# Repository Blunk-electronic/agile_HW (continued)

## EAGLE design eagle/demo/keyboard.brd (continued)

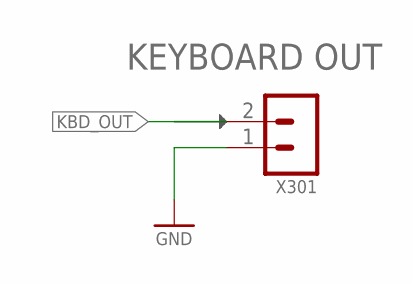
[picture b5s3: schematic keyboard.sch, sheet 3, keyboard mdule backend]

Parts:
X301: MALE_2X1-T-VERTICAL; T_MALE_2X1_VERTICAL_PITCH_2MM54

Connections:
GND: X301.1; also elsewhere on the board
KBD_OUT: X301.2; also elsewhere on the board

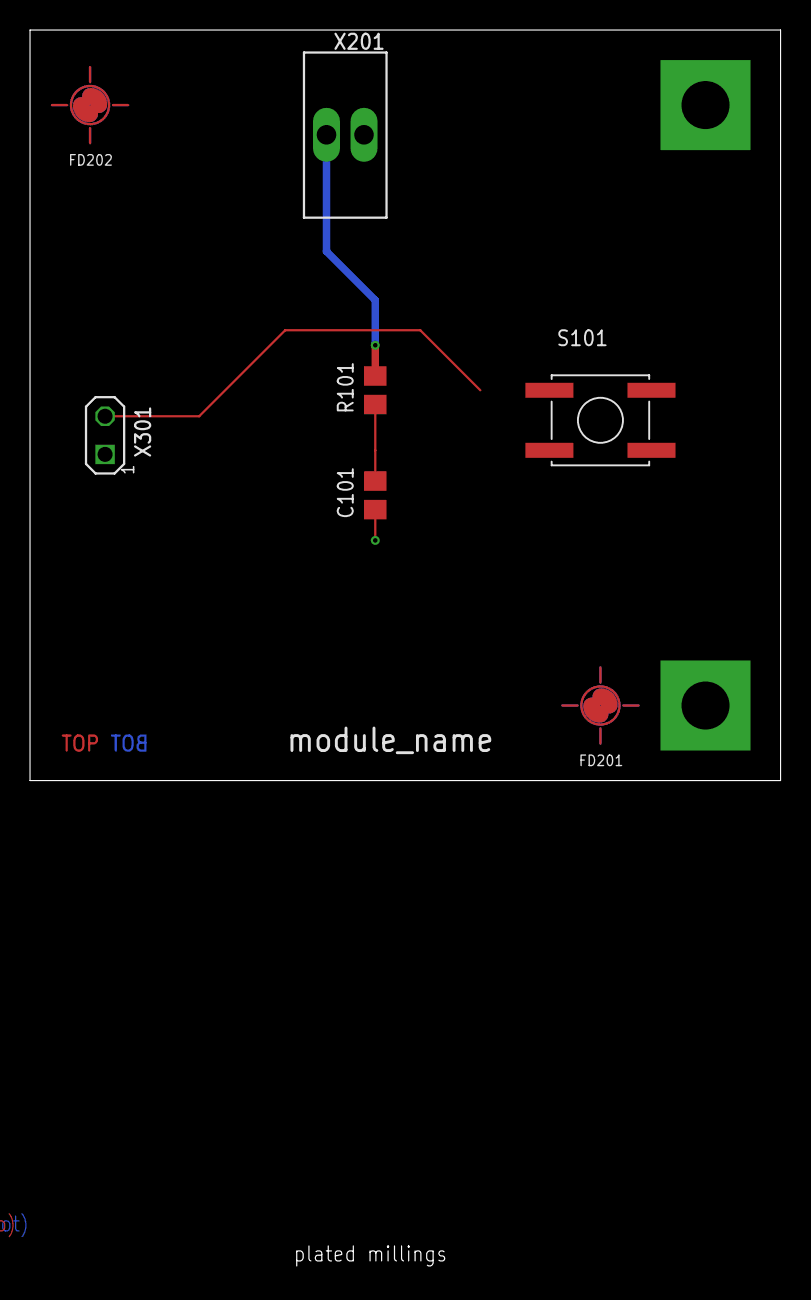
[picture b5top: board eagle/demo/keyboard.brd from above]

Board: 4 copper layers, 50.0 x 82.6 mm, 10 parts (0 on the bottom side), 3 nets.

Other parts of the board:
U$5: A4_LANDSCAPE

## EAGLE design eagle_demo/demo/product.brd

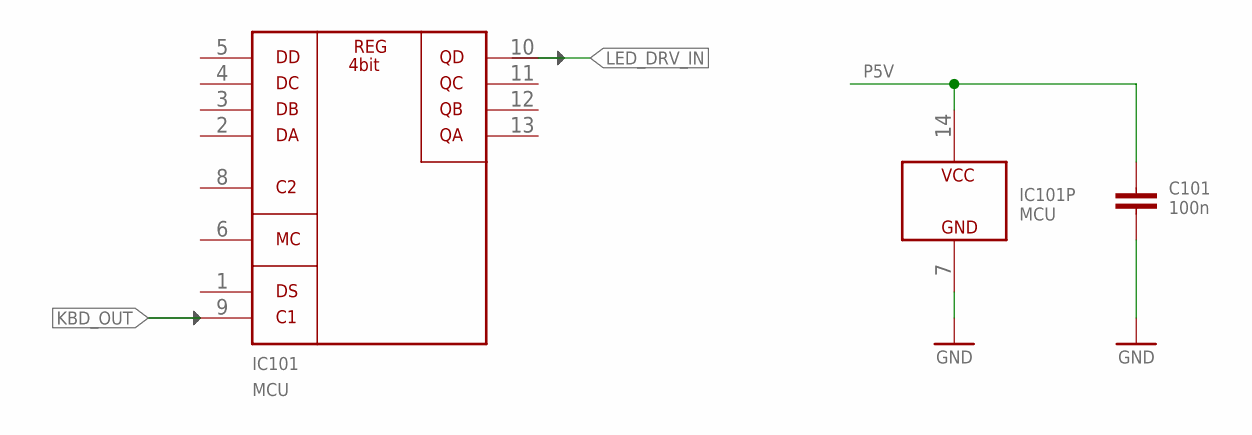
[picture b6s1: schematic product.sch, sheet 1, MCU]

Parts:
C101: 100n; S_0603
IC101: MCU; S_SO14

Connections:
GND: C101.2, IC101.7 (GND); also elsewhere on the board
KBD_OUT: IC101.9 (C1); also elsewhere on the board
LED_DRV_IN: IC101.10 (QD); also elsewhere on the board
P5V: C101.1, IC101.14 (VCC); also elsewhere on the board

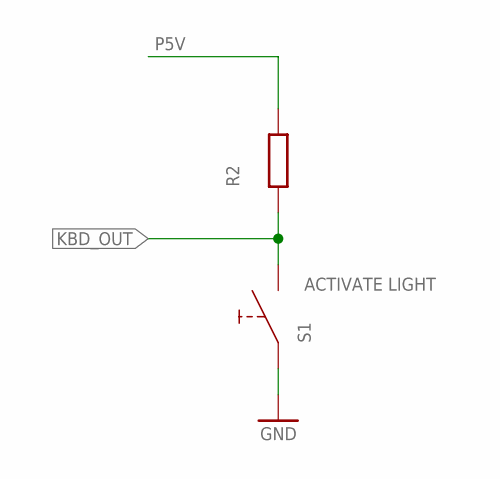
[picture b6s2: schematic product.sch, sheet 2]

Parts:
R2: R_S_0603; S_0603
S1: PUSH_BUTTON_S_6X6MM; S_PUSH_BUTTON_6X6

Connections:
GND: S1.A (A1), S1.A1; also elsewhere on the board
KBD_OUT: R2.1, S1.B (B1), S1.B1; also elsewhere on the board
P5V: R2.2; also elsewhere on the board

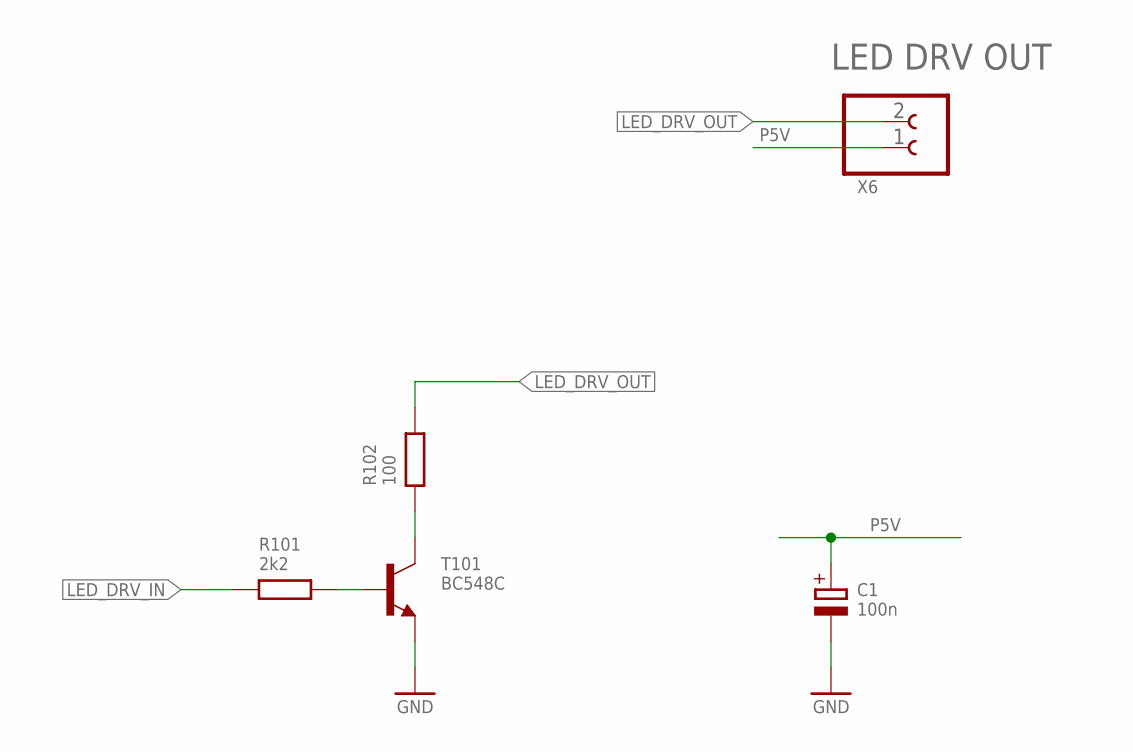
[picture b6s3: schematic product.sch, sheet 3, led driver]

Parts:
C1: 100n; S_3216-18
R101: 2k2; S_0603
R102: 100; S_0603
T101: BC548C; S_SOT23
X6: CLAMP_1X2-T-2.5MM; T_WIRE_CLAMP_1X2_PITCH_2MM5

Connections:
GND: C1.-, T101.2 (E); also elsewhere on the board
LED_DRV_B: R101.2, T101.1 (B)
LED_DRV_C: R102.1, T101.3 (C)
LED_DRV_IN: R101.1; also elsewhere on the board
LED_DRV_OUT: R102.2, X6.2
P5V: C1.+, X6.1; also elsewhere on the board

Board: 2 copper layers, 9 parts (0 on the bottom side), 7 nets, no tracks yet.

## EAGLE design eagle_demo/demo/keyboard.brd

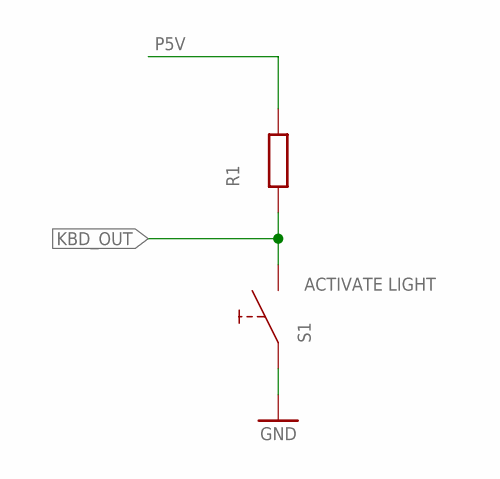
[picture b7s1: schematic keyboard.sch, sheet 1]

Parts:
R1: R_S_0805; S_0805
S1: PUSH_BUTTON_S_6X6MM; S_PUSH_BUTTON_6X6

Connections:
GND: S1.A (A1), S1.A1; also elsewhere on the board
KBD_OUT: R1.1, S1.B (B1), S1.B1; also elsewhere on the board
P5V: R1.2; also elsewhere on the board

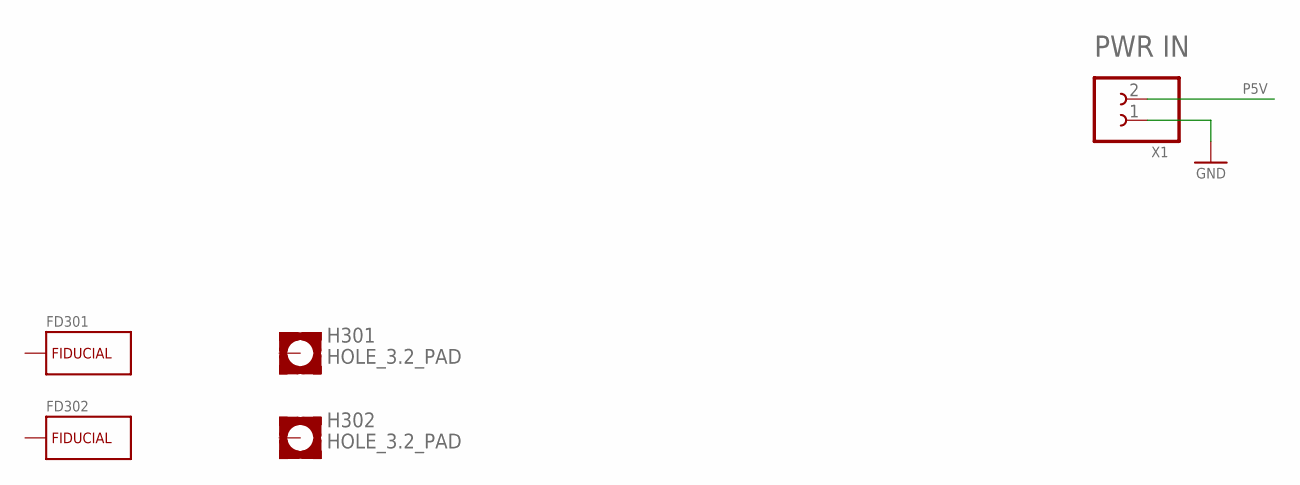
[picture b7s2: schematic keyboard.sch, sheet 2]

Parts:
FD301, FD302: FIDUCIAL_CROSSHAIR; CROSSHAIR
H301, H302: HOLE_3.2_PAD; 3.2_PAD
X1: CLAMP_1X2-T-2.5MM; T_WIRE_CLAMP_1X2_PITCH_2MM5

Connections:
GND: X1.1; also elsewhere on the board
P5V: X1.2; also elsewhere on the board

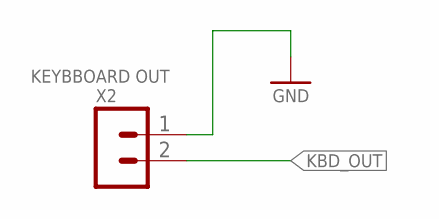
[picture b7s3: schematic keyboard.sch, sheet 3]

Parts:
X2: MALE_2X1-T-VERTICAL; T_MALE_2X1_VERTICAL_PITCH_2MM54

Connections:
GND: X2.1; also elsewhere on the board
KBD_OUT: X2.2; also elsewhere on the board

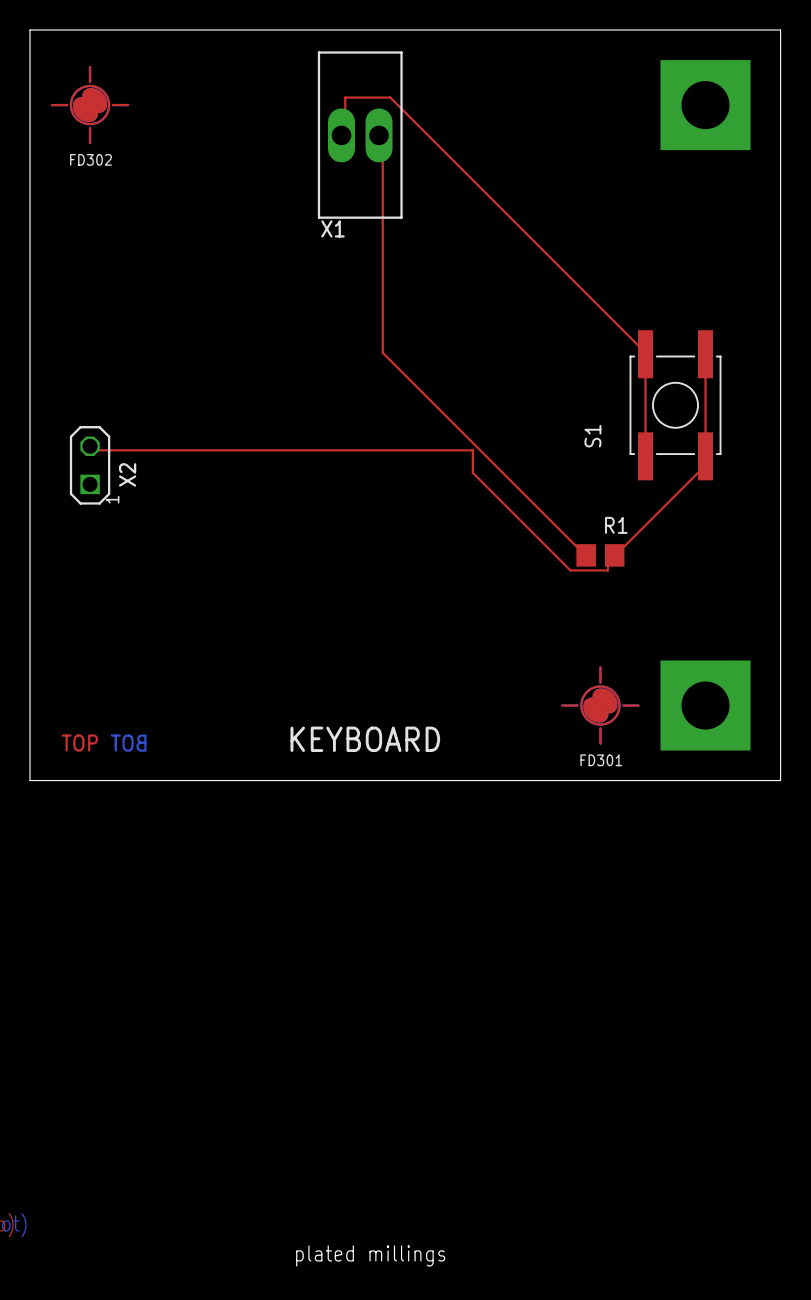
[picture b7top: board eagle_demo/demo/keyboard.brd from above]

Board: 4 copper layers, 50.0 x 82.6 mm, 9 parts (0 on the bottom side), 3 nets.

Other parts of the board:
U$5: A4_LANDSCAPE

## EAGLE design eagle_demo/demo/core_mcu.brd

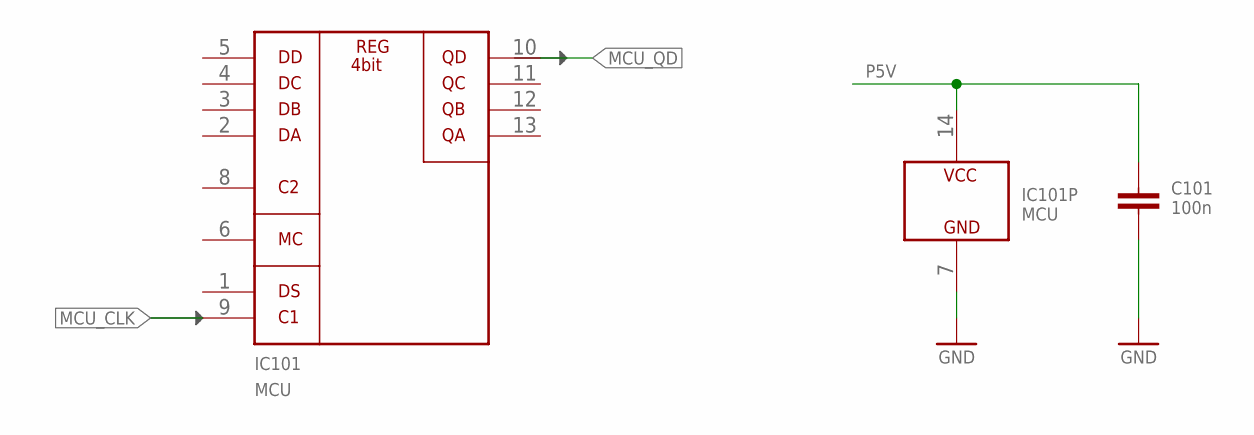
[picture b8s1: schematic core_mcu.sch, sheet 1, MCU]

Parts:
C101: 100n; S_0805
IC101: MCU; T_NDIP14

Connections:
GND: C101.2, IC101.7 (GND); also elsewhere on the board
MCU_CLK: IC101.9 (C1); also elsewhere on the board
MCU_QD: IC101.10 (QD); also elsewhere on the board
P5V: C101.1, IC101.14 (VCC); also elsewhere on the board

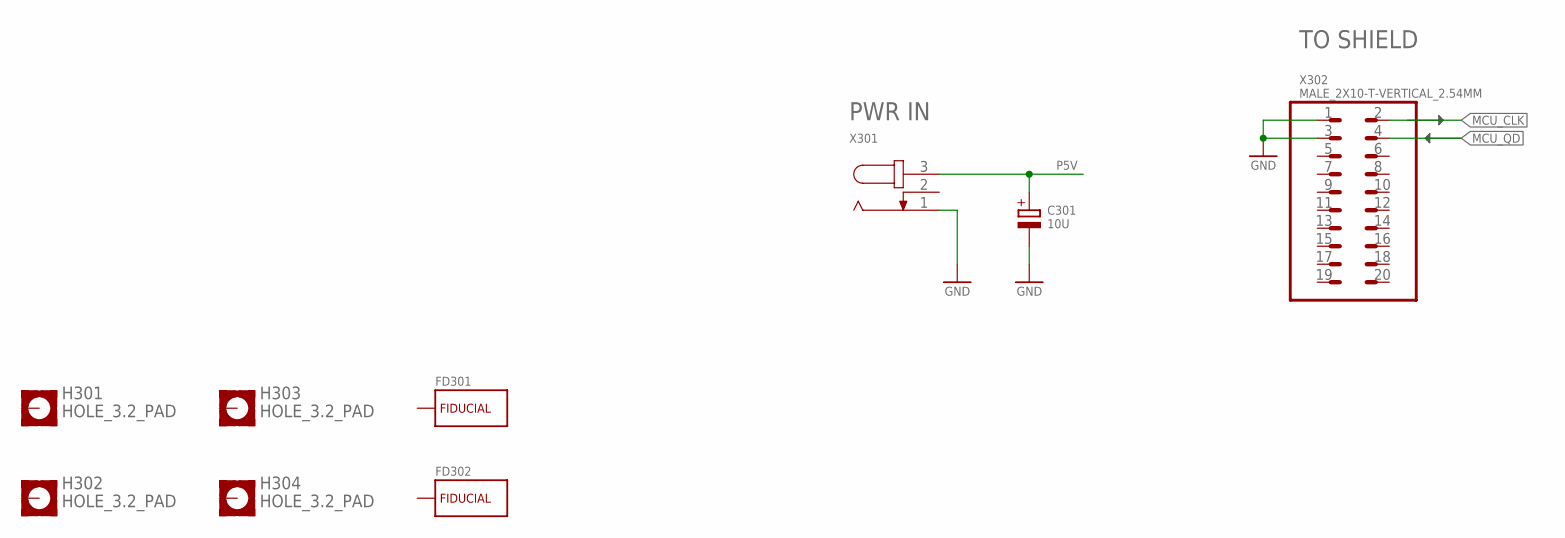
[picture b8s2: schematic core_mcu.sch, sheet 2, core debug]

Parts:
C301: 10U; S_6032
FD301, FD302: FIDUCIAL_CROSSHAIR; CROSSHAIR
H301, H302, H303, H304: HOLE_3.2_PAD; 3.2_PAD
X301: POWER_JACK-T-0; T_POWER_JACK_SPC4077
X302: MALE_2X10-T-VERTICAL_2.54MM; T_MALE_2X10_VERTICAL_GRID_2.54MM

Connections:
GND: C301.-, X301.1, X302.1, X302.3; also elsewhere on the board
MCU_CLK: X302.2; also elsewhere on the board
MCU_QD: X302.4; also elsewhere on the board
P5V: C301.+, X301.3; also elsewhere on the board

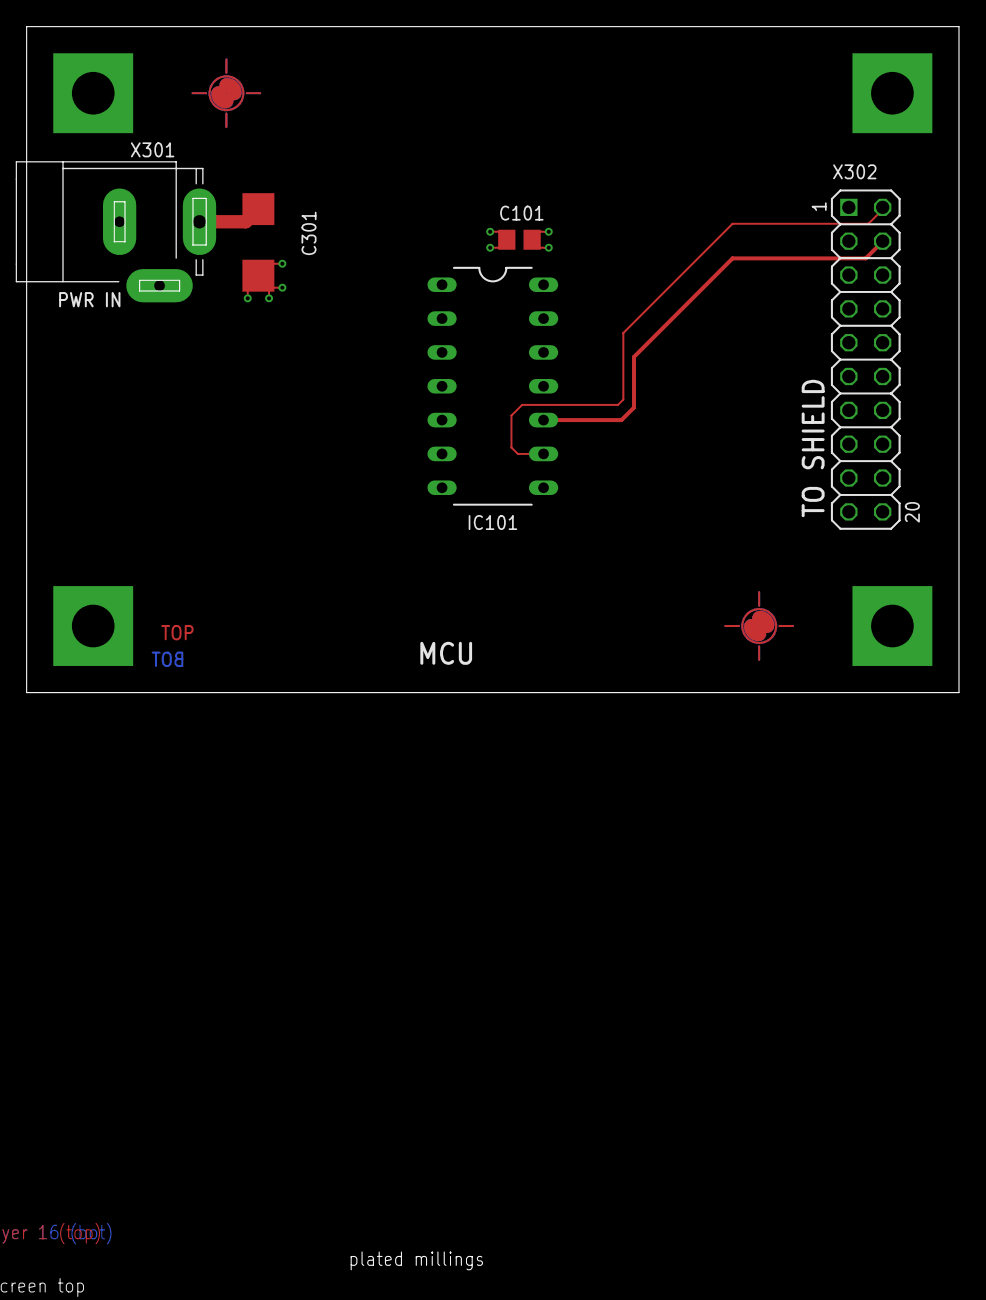
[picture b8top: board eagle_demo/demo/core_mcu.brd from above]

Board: 4 copper layers, 70.0 x 93.6 mm, 12 parts (0 on the bottom side), 4 nets.

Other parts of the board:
U$9: A4_LANDSCAPE

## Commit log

2018-08-18 first demo files
2018-08-20 kbd module
2018-08-20 fixed led driver
2018-08-20 finished core
2018-08-20 fixed prefixes
2018-08-20 name schematic sheets
2018-08-20 step 1: merge schematics
2018-08-20 step 2: delete dev. pages
2018-08-20 step 3a: reduce routing page
2018-08-20 step 3b: remove routing page
2018-08-20 step 4: add prod. spec. sheet
2018-08-20 step 5: place parts in product layout
2018-08-20 step 6: route pwr
2018-08-20 step 7: finish routing
2018-08-20 step 8: replace MCU package
2018-08-20 fix: update schematic
2018-08-20 pro file
2018-08-27 - blockschaltbild für einen LED treiber - blockschaltbild für zwei LED treiber
    - Die Blockschaltbilder hätten im Stadium "merge schematics" eingefügt werden sollen.
    - Wenn das nachträglich noch geht, wär gut.
2018-08-27 fix dir of block schematic
2018-08-27 instantiated two led drivers
2018-08-27 shield for two drivers
2018-08-27 fix silk screen
2018-10-23 step 0
2018-10-23 fix core device
2018-10-23 fix template
2018-10-23 instructions added
2018-10-23 step 2.1.2 dev pages removed
2018-10-23 step 1.1 block diagram update
2018-10-23 step 1.2 keyboard schematic
2018-10-23 step 1.5 shield layout
2018-10-23 step 1.3 shield schematic updated
2018-10-23 step 1.4 keyboard layout
2018-10-23 step 2.1.1 schematic all in one
2018-10-23 step 2.3 product layout placement
2018-10-23 step 2.2 reduce routing
2019-02-01 demo at ASK finished
2019-03-17 readme files
2019-04-15 fix partcodes
2019-04-16 instantiate led_drivers 1 and 2. board file not relevant
2019-04-16 fix net names
2019-04-16 clean-up script
2019-05-06 readme in bom directory
2019-05-06 clean up in bom directory
2019-05-06 improve clean up
2020-04-08 start instantiator script
2020-04-10 extract base name
2020-04-16 schematic instantiation complete
2020-04-16 board instantiation complete
2020-04-16 rename to instantiate
2020-04-16 install instructions
2020-04-16 example
